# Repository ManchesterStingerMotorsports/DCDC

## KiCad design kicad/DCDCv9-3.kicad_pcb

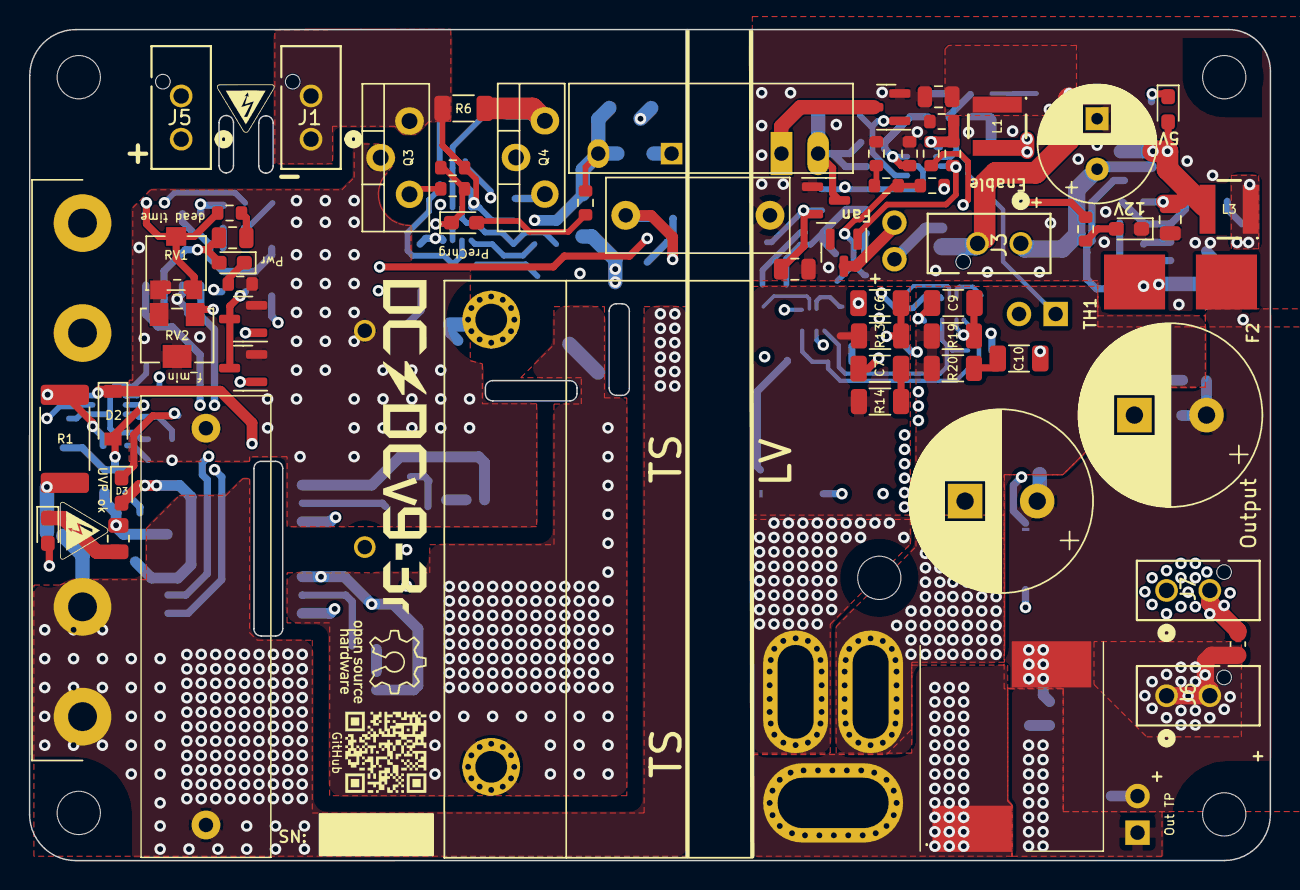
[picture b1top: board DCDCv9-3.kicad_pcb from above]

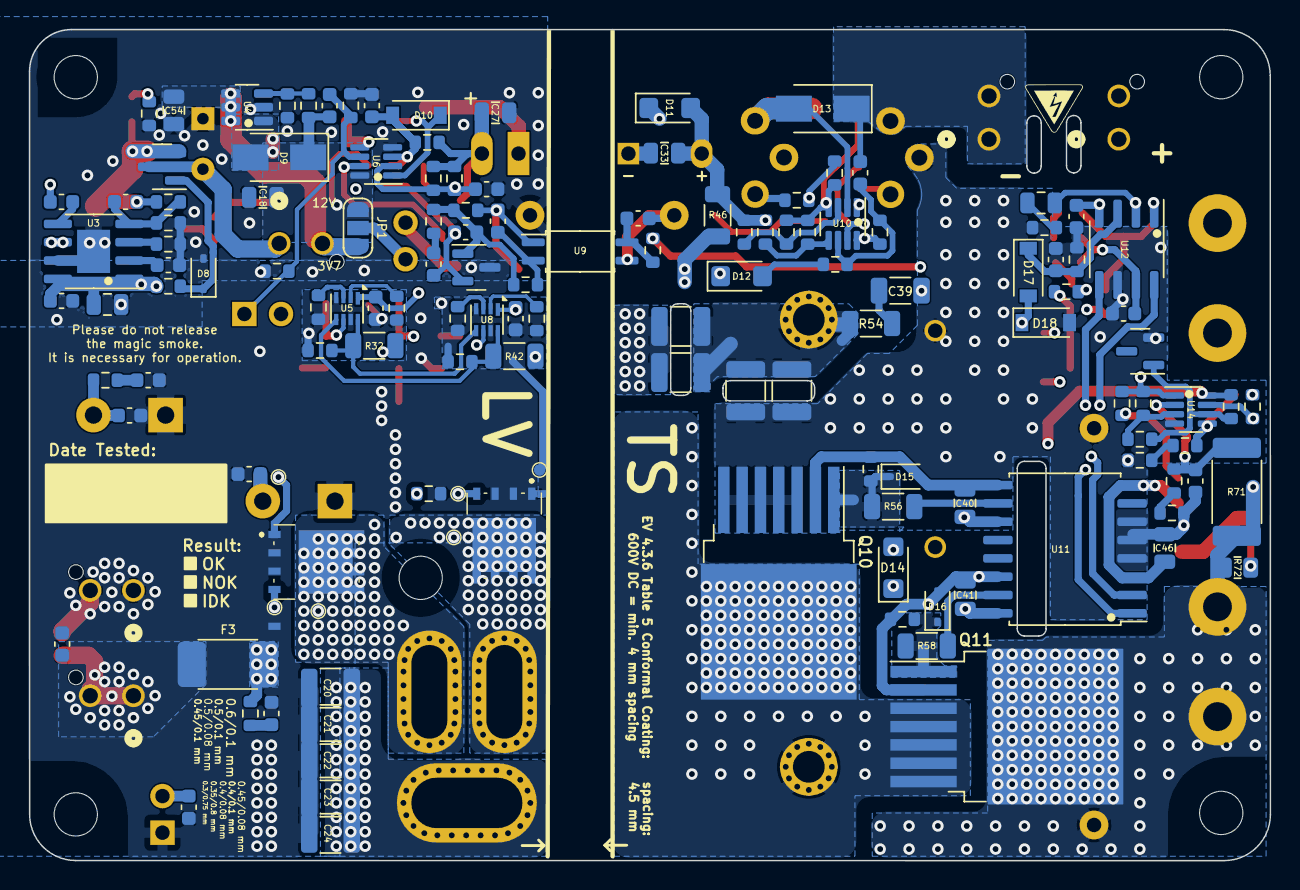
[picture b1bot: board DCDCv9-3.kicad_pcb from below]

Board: 4 copper layers, 86.0 x 57.6 mm, 208 parts (138 on the bottom side), 102 nets.

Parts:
C1: 2uF; MKP1848520704K2
C2, C15, C40, C41: 2.2uF; C_0805_2012Metric
C3: 22nF; R76UI22205050J
C4: 3.3nF; C_Disc_D12.5mm_W5.0mm_P10.00mm
C5, C33, C46: 10uF; C_0805_2012Metric
C6, C9: 1 nF; C_1206_3216Metric
C7, C10, C39: 470pF; C_1206_3216Metric
C8, C12, C18, C27, C42, C54: 22uF; C_0805_2012Metric
C11, C13: 2200uF; CP_Radial_D12.5mm_P5.00mm_symbol_inside
C14, C28: 100nF; C_0603_1608Metric
C16, C49, C50, C51, C52, C53, C55, C56, C57: 1nF; C_0603_1608Metric
C17, C19, C25, C31, C45: 1uF; C_0603_1608Metric
C20, C21, C22, C23, C24: 10uF; C_1210_3225Metric
C26, C44, C47: 22nF; C_0603_1608Metric
C29: 47pF; C_0603_1608Metric
C30, C32, C48: 10nF; C_0603_1608Metric
C34, C35, C36, C37: 5.6nF; C_1210_3225Metric
C38: 120pF; C_0603_1608Metric
C43: 470nF; C_0603_1608Metric
C_start1: 3.8V 25F Supercap; CP_Radial_D8.0mm_P3.50mm
D1: HV_Orange; LED_0603_1608Metric_Pad1.05x0.95mm_HandSolder
D2, D10, D17, D18: 1N4448; D_SOD-123
D3, D4, D5, D6, D7: Green; LED_0603_1608Metric_Pad1.05x0.95mm_HandSolder
D8, D15, D16: CDSOD323-T12; D_SOD-323
D9, D13: SS1H10; D_SMA
D11, D12, D14: VS-E7FX0212-M3/I; D_SMF
F1: 1.6A; Fuseholder0,25Zoll_32mm_littlefuse_102_122
F2: 500mA; NANO-0154-OMNI-BLOK-Fuse-Holder
F3: 20A; Bel_SMCF_Fuse_2410_6125Metric
HV_Logo_1, HV_Logo_1#2, HV_Logo_1#3: HV_Logo_1; HV_Logo_small
J1, J3, J5, J6, J7: Molex Vert; Molex Microfit Vert
J2, J4, J8: Conn_01x02_Male; PinHeader_1x02_P2.54mm_Vertical
JP1: Fan Voltage Select; SolderJumper-3_P1.3mm_Open_RoundedPad1.0x1.5mm_NumberLabels
L1: 4.7uH; ASPI-4030S
L2: 1uH; 7443091100_v9.2
L3: 10uH; ASPI-4030S
NT1, NT2: NetTie_2; dummy_net_line_0.5mm
Q1, Q2, Q5, Q6, Q7: PMV20ENR; SOT-23
Q3: SIHP24N80AE-GE3; TO-220-3_Vertical_HV1.2mm
Q4: IXYP8N90C3; TO-220-3_Vertical_HV1.2mm
Q8, Q9: BSC027N06LS5ATMA1
Q10, Q11: IMBG65R050M2HXTMA1; TO-263-7_TabPin8
QR_Coode_1: QR_Coode; GitHub_QR_Code
R1, R71: 100M; R_2512_6332Metric_Pad1.40x3.35mm_HandSolder
R2, R72: 330k; R_0805_2012Metric
R3: 3.0k; R_0603_1608Metric
R4, R39, R41, R59, R61: 1k; R_0603_1608Metric
R5, R7, R9, R11, R15, R16, R21, R23, R30, R33, R40, R43, R51, R52, R55, R57, R63: 10k; R_0603_1608Metric
R6, R14, R20: 47; R_1206_3216Metric
R8, R10, R22, R29, R38, R48, R49: 2.2k; R_0603_1608Metric
R12: 910; R_0603_1608Metric
R13, R19: 100; R_1206_3216Metric
R17, R24: 27k; R_0603_1608Metric
R18, R27, R50: 470k; R_0603_1608Metric
R25: 240k; R_0603_1608Metric
R26, R45, R47, R53, R67, R70, R75: 100k; R_0603_1608Metric
R28, R34, R66: 33k; R_0603_1608Metric
R31, R36: 4.7k; R_0603_1608Metric
R32, R42: 4.7; R_1206_3216Metric
R35: 330k; R_0603_1608Metric
R37: 47k; R_0603_1608Metric
R44: 510; R_0603_1608Metric
R46: 20; R_1206_3216Metric
R54: 10M; R_1206_3216Metric
R56, R58: 10; R_1206_3216Metric
R60: 82k; R_0603_1608Metric
R62, R69: 100M; R_0603_1608Metric
R64: 820k; R_0603_1608Metric
R65: 510k; R_0603_1608Metric
R68: 1.6M; R_0603_1608Metric
R73, R74: 10; R_0603_1608Metric
RV1: 20k; Potentiometer_Bourns_PVG3G
RV2: 10k; Potentiometer_Bourns_3214W_Vertical
T1: DIY Transformer ETD 39; Transformer_ETD39_uprightV3.6 (PSS 24V)
TH2: 1k PTC; R_0603_1608Metric
TP1, TP2, TP3, TP4, TP5, TP6: TestPoint; TestPoint_Pad_D0.8mm_DC-DC
TP8: GaN GND2; TestPoint_Pad_D0.8mm_DC-DC
U1: RP-1212S; Converter_DCDC_TRACO_TBA 1-1212HI-3kV-iso
U2: RT9058-90GVL; SOT-23
U3: MP4541_SOP8-EP; SOIC-8-1EP_3.9x4.9mm_P1.27mm_EP2.29x3mm XL7005
U4: TLV61048DBVR; SOT-23-6
U5, U8: NCP4305DMTTWG; WDFN-8_2x2mm_P0.5mm
U6, U10, U14: LM2904BIDDFR; SOT-23-8_DC-DC_v9
U7: TL431BCDBZR; SOT-23
U9: ACPL-217-50AE; SOIC-4_4.55x2.6mm_P1.27mm
U11: UCC21520DW; SOIC-16W_7.5x10.3mm_P1.27mm
U12: UCC25600; SOIC-8_3.9x4.9mm_P1.27mm
U13: ZXRE330ASA-7; SOT-23

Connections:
24V_TP: C11.1, C13.1, C50.2, C51.2, C52.2, F2.1, F3.1, J4.1, L2.2, R17.1, R73.1, R74.1
+3V7: C8.1, C54.1, J3.2, JP1.3 (B), L1.1, U4.4 (~SHDN), U4.5 (IN), U4.6 (nc)
+9V: C5.1, C30.2, R39.1, U2.2 (VO), U9.1
+12V_HS: C41.2, D14.1 (K), U11.16 (VDDA)
+12V_IN: C2.2, C40.2, C45.2, C46.1, D2.1 (K), D3.2 (A), D4.2 (A), D11.1 (K), R70.1, U11.3 (VCCI), U11.8 (VCCI), U11.11 (VDDB), U12.7 (VCC), U14.8 (V+)
+12V_sw: C18.1, C19.2, C25.1, C27.1, C31.1, D9.1 (K), J8.1, JP1.1 (A), R16.1, R21.2, R27.1, R34.1, R35.2, R36.2, U1.1 (+VIN), U2.3 (VI), U5.1 (VCC), U6.8 (V+), U8.1 (VCC)
+24V: C15.2, C53.2, F2.2, R26.2, U3.1 (EN), U3.8 (VIN)
+HV: C1.2, C34.1, C35.1, F1.2, Q11.8 (D), R1.1, R71.1, R72.1
+HV_in: F1.1, J5.1, J5.2
-HV_in: C33.2, C38.1, D13.1 (K), J1.1, J1.2, Q3.3 (S), R6.2, R7.2, R48.1, R50.1, R51.2, U1.5 (-VOUT), U10.4 (V-)
-HV_pc: C1.1, C3.2 (2_2), C4.1, C32.2, C36.2, C37.2, C43.2, C44.1, C45.1, C46.2, C47.2, D12.1 (K), D18.2 (A), Q1.2 (S), Q2.2 (S), Q3.2 (D), Q4.2 (C), Q10.3 (S), Q10.4 (S), Q10.5 (S), Q10.6 (S), Q10.7 (S), R2.2, R3.2, R5.1, R59.2, R60.1, R65.2, R68.2, RV1.3, RV2.2, RV2.3, U9.3, U11.4 (GND), U11.5 (DIS), U11.6 (DT), U12.6 (GND), U13.2, U14.4 (V-)
/HB_out: Q10.8 (D), Q11.3 (S), Q11.4 (S), Q11.5 (S), Q11.6 (S), Q11.7 (S), T1.1 (AA)
/HS: U11.1 (INA), U12.8 (GD1)
/LS: U11.2 (INB), U12.5 (GD2)
/OC: C44.2, D17.1 (K), R60.2, U12.3 (OC)
/OTP_FAN: Q5.1 (G), R18.1, U6.7
/OTP_OFF: D10.1 (K), Q6.1 (G), U6.1
/OVP: Q2.1 (G), R69.1, U14.7
/Opc+: C32.1, R44.2, U9.4
/Synchronous Rectification/3: Q9.5 (D_1), Q9.6 (D_2), Q9.7 (D_3), Q9.8 (D_4), Q9.9 (D_5), R13.2, R14.1, T1.3 (SB), TP5.1 (1_1)
/Synchronous Rectification/5: Q8.5 (D_1), Q8.6 (D_2), Q8.7 (D_3), Q8.8 (D_4), Q8.9 (D_5), R19.2, R20.1, T1.5 (SA), TP3.1 (1_1)
/UVP: Q1.1 (G), R62.1, R63.1, U14.1
GND: C4.2, C5.2, C7.1, C8.2, C10.1, C11.2, C12.1, C13.2, C15.1, C17.1, C18.2, C20.2, C21.2, C22.2, C23.2, C24.2, C27.2, C28.1, C48.1, C49.1, C50.1, C51.1, C52.1, C53.1, C54.2, C55.1, C56.1, C57.1, C_start1.2 (-), D6.1 (K), D8.2 (A2), J4.2, J7.1, J7.2, NT1.2, NT2.2, Q5.2 (S), Q6.2 (S), Q8.1 (S_1), Q8.2 (S_2), Q8.3 (S_3), Q9.1 (S_1), Q9.2 (S_2), Q9.3 (S_3), R10.2, R11.2, R15.1, R22.1, R23.2, R25.1, R28.2, R31.1, R75.2, TH2.2, TP8.1, U2.1 (GND), U3.7 (GND), U4.2 (GND), U6.4 (V-), U7.3 (A)
unnamed: C2.1, R4.2
unnamed: C7.2, R14.2
unnamed: C10.2, R20.2
unnamed: C26.2, R37.1
unnamed: C30.1, R41.1, U9.2
unnamed: C39.2, R54.1
unnamed: C42.2, R59.1
unnamed: C49.2, C55.2, F3.2, J6.1, J6.2
unnamed: C56.2, R73.2
unnamed: C57.2, R74.2
unnamed: C_start1.1 (+), J3.1, Q7.3 (D)
unnamed: D1.2 (A), R72.2
unnamed: D1.1 (K), R2.1
unnamed: C47.1, D2.2 (A), R67.2, R71.2, U14.2 (-)
unnamed: D3.1 (K), R63.2
unnamed: D4.1 (K), R5.2
unnamed: D5.2 (A), R9.1
unnamed: D5.1 (K), R7.1, R8.2, U10.7
unnamed: D6.2 (A), R21.1
unnamed: C12.2, C16.2, D7.2 (A), L3.2, Q7.2 (S), R24.1
unnamed: D7.1 (K), R22.2
unnamed: D8.1 (A1), Q7.1 (G), R26.1
unnamed: D9.2 (A), L1.2, U4.1 (SW)
unnamed: C48.2, D10.2 (A), R11.1, R34.2, U6.3 (+)
unnamed: C33.1, D11.2 (A), R9.2, R45.2, R46.2, R47.2, R53.2, U1.7 (+VOUT), U10.8 (V+)
unnamed: D12.2 (A), R52.1
unnamed: D13.2 (A), Q4.3 (E), R6.1, U10.2 (-)
unnamed: D14.2 (A), R46.1
unnamed: D15.1 (A1), Q10.1 (G), R55.1, R56.1
unnamed: C40.1, D15.2 (A2), Q10.2 (DS), R55.2, U11.9 (VSSB)
unnamed: D16.1 (A1), Q11.1 (G), R57.1, R58.1
unnamed: C41.1, D16.2 (A2), Q11.2 (DS), R57.2, U11.14 (VSSA)
unnamed: C39.1, D17.2 (A), D18.1 (K)
unnamed: J2.1, JP1.2 (C)
unnamed: J2.2, Q5.3 (D)
unnamed: C19.1, J8.2, R31.2, R75.1, U6.6 (-)
unnamed: Q1.3 (D), Q2.3 (D), R61.1
unnamed: Q3.1 (G), R8.1
unnamed: Q4.1 (G), R49.1
unnamed: Q8.4 (G), R32.1, TP2.1 (1_1)
unnamed: Q9.4 (G), R42.1, TP4.1 (1_1)
unnamed: R10.1, R12.2
unnamed: R49.2, R51.1, U10.1
unnamed: R65.1, R66.2
unnamed: R67.1, R68.1
unnamed: C34.2, C35.2, C36.1, C37.1, R54.2, T1.2 (AB)
unnamed: C20.1, C21.1, C22.1, C23.1, C24.1, L2.1, T1.4 (SC)
unnamed: C14.2, U3.5 (BST)
unnamed: C16.1, R23.1, R24.2, U3.4 (FB)
unnamed: R25.2, U3.3 (FREQU)
unnamed: C14.1, L3.1, U3.6 (SW)
unnamed: C17.2, U3.2 (VCC)
unnamed: R27.2, R28.1, U4.3 (FB)
unnamed: C9.2, R19.1, U5.6 (CS)
unnamed: R30.2, R32.2, U5.8 (DRV), U8.5 (TRIG/DIS)
unnamed: C9.1, C25.2, NT1.1, R29.1, R30.1, R33.1, TP1.1 (1_1), U5.4 (LLD), U5.7 (GND)
unnamed: R33.2, U5.2 (MIN_TOFF)
unnamed: R29.2, U5.3 (MIN_TON)
unnamed: R40.2, R42.2, U5.5 (TRIG/DIS), U8.8 (DRV)
unnamed: C28.2, R35.1, R36.1, TH2.1, U6.2 (-)
unnamed: R15.2, R16.2, R18.2, U6.5 (+)
unnamed: C29.2, R37.2, R39.2, R41.2, U7.1 (K)
unnamed: C26.1, C29.1, R12.1, R17.2, U7.2 (REF)
unnamed: C6.2, R13.1, U8.6 (CS)
unnamed: C6.1, C31.2, NT2.1, R38.1, R40.1, R43.1, TP6.1 (1_1), U8.4 (LLD), U8.7 (GND)
unnamed: R43.2, U8.2 (MIN_TOFF)
unnamed: R38.2, U8.3 (MIN_TON)
unnamed: R45.1, R48.2, U10.3 (+)
unnamed: R47.1, R50.2, U10.5 (+)
unnamed: C38.2, R52.2, R53.1, U10.6 (-)
unnamed: R58.2, U11.15 (OUTA)
unnamed: R56.2, U11.10 (OUTB)
unnamed: R3.1, R4.1, RV1.1, RV1.2, U12.1 (DT)
unnamed: C42.1, R44.1, RV2.1, U12.2 (RT)
unnamed: C43.1, R61.2, U12.4 (SS)
unnamed: R62.2, R64.1, U14.3 (+)
unnamed: R1.2, R66.1, R69.2, U14.5 (+)
unnamed: R64.2, R70.2, U13.1, U14.6 (-)
OTP_FET: Q6.3 (D), U1.2 (-VIN)
